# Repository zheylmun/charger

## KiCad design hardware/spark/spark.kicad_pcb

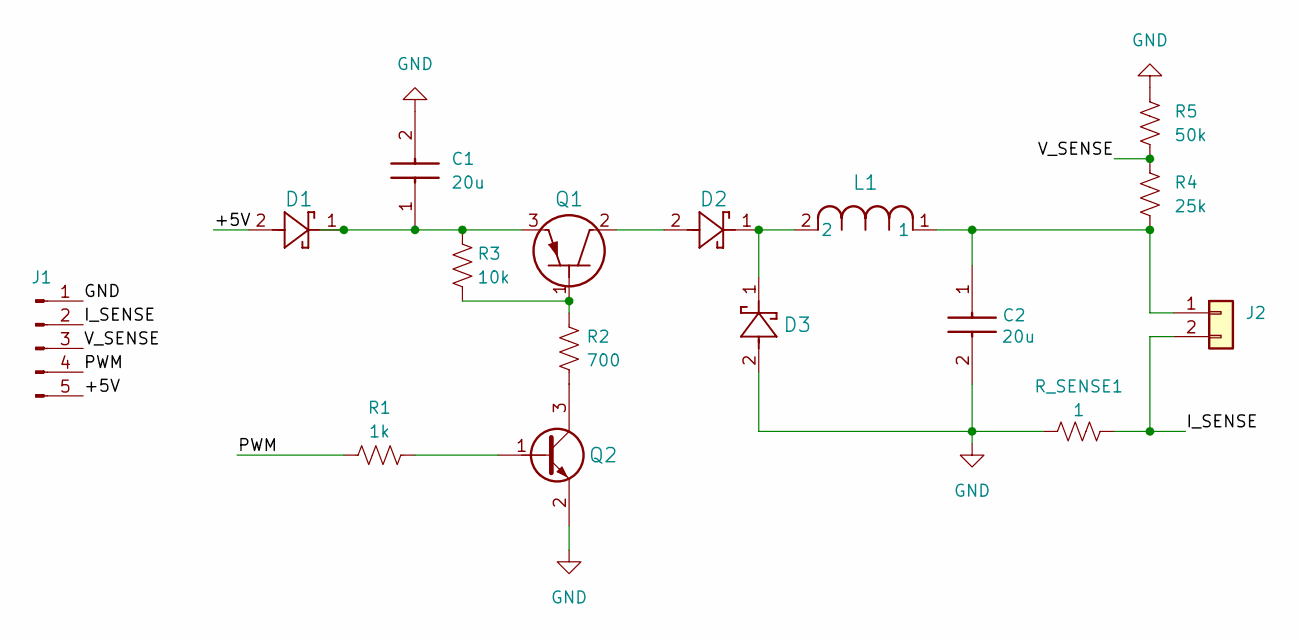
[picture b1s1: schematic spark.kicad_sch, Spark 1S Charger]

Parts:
C1, C2: 20u; DIOM7959X262N; Mouser Part Number 81-GRMJN7R61C206ME5D
D1, D2, D3: MBR120VLSFT1G; SDO_SOD-123FL_ONS
J1: Conn_01x05_Pin; PinHeader_1x05_P2.54mm_Vertical
J2: Conn_01x02; PinHeader_1x02_P2.54mm_Vertical
L1: SRR1260-151K; IND_BOURNS_SRR1260
Q1: STD2805T4; DPAKTO-252_TYPEA_STM
Q2: PMBT2369; SOT23_NXP
R1: 1k; R_0402_1005Metric
R2: 700; R_0402_1005Metric
R3: 10k; R_0402_1005Metric
R4: 25k; R_0402_1005Metric
R5: 50k; R_0402_1005Metric
R_SENSE1: 1; R_0402_1005Metric

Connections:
/+5V: D1.2, J1.5
/I_SENSE: J1.2, J2.2, R_SENSE1.2
/PWM: J1.4, R1.1
/V_SENSE: J1.3, R4.1, R5.2
GND: C1.2, C2.2, D3.2, J1.1, Q2.2, R5.1, R_SENSE1.1
unnamed: C1.1, D1.1, Q1.3, R3.1
unnamed: D2.1, D3.1, L1.2
unnamed: D2.2, Q1.2
unnamed: C2.1, J2.1, L1.1, R4.2
unnamed: Q1.1, R2.1, R3.2
unnamed: Q2.1, R1.2
unnamed: Q2.3, R2.2

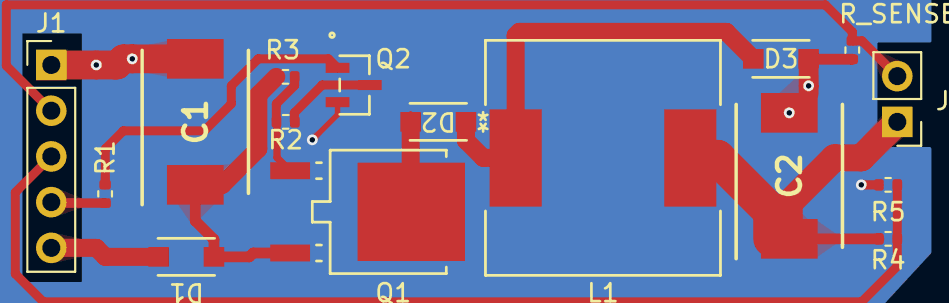
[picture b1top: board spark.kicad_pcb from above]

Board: 2 copper layers, 16 parts (0 on the bottom side), 12 nets.

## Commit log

2025-04-14 Check in initial schematic and important libraries
2025-05-02 Add library components and layout basics
2025-05-06 First pass routing of traces
2025-05-06 Cleanup
